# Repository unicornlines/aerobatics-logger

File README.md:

# Aerobatics Flight Logger

An onboard flight data logger and an Apple debrief app (iOS, iPadOS, macOS) for aerobatics training.

The specification lives in the project's spec document. This repository holds:

- `hardware/`: the KiCad schematic and PCB
- `firmware/`: the STM32H723 on-board firmware (planned)
- `app/`: the SwiftUI debrief app (planned)

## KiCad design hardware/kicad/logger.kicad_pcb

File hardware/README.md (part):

# Hardware

Rev A draft schematic and board for the logger, in KiCad 7 format. Both are generated from code:

- `tools/design.py`: every part and every pin's net. **Edit this, not the `.kicad_sch` files.**
- `tools/mklib.py`: builds `kicad/logger.kicad_sym` for parts KiCad doesn't ship (ICM-45686, BMP390, BMM350, NEO-M9N, ESP32-C6-MINI-1, GD5F4GM8UE), with pin tables from the datasheets.
- `tools/gen.py`: writes the sheets under `kicad/`, joining nets with global labels and flagging unused pins.
- `tools/check.py`: connectivity checks on the exported netlist (every assigned pin is on its net, power nets are driven, no output conflicts). It stands in for ERC, which the KiCad 7 command line doesn't have.

```sh
cd hardware/tools
python3 mklib.py && python3 gen.py
kicad-cli sch export netlist ../kicad/logger.kicad_sch -o /tmp/logger.net
python3 check.py /tmp/logger.net
kicad-cli sch export pdf ../kicad/logger.kicad_sch -o ../kicad/logger.pdf
```

`kicad/logger.pdf` is the latest export, for review without KiCad.

## Board

- 138 x 62 mm, 4 layers, 1.6 mm: F.Cu signals and GND pour, In1 solid GND, In2 +3V3 pour with a few signal runs, B.Cu signals and GND pour. Every part is SMD; the only parts on the back are the three key sockets. The outline is a plain rounded rectangle with no cut-outs or slots, since the board takes repeated g loads in aerobatics.
- Rules: 0.15 mm track and clearance, 0.5/0.25 mm vias, 0.4 mm for the power path.
- Front face: the Sharp 2.7-inch memory LCD at the top (7 mm right of the board's centre since the left end grew 14 mm for the GNSS patch), the three keys (UP, OK / PWR, DOWN) centred under it. Under the panel only parts up to 2.9 mm tall: the MCU with its crystals, the log flash, the 3.3 V buck and the LCD's 5 V boost and FPC socket.
- Floor plan around the panel: radio (top-left corner, antenna up), the GNSS module and its built-in patch antenna on the left, sensors below them; USB-C and microSD on the right short edge (the card goes in through the case wall), the charger, USB protection and power latch beside them; the battery socket (plug in from the right edge) and its protection in the bottom-right corner, with the logo beside the DOWN key. Passives sit in straight rows and columns next to the pins they serve.
- Top edge: radio antenna, Qwiic socket (J63), camera/marker socket (J62, JST SUR, for a lead inside the case) and the LCD's FPC fold.
- The IMU moved from the Bosch BMI563 (still not on sale) to the TDK ICM-45686 on 2026-11-25.
- The magnetometer sits at the left end, as far as possible from the buck and the battery currents; the barometer sits bottom-left beside the UP key at (22.5, 53.5), with a part-free ring round it where the case seals its hood: open to cockpit air, or with a barb for the static-port hose.
- Environmental chamber: the Sensirion SHT40 (cockpit temperature and humidity) and the top-port microphone sit together at the left edge, in one chamber the case walls off and vents through the left side wall (no openings in the face). The SHT40 sits on a copper-free island (no pour on any layer, 0.15 mm traces) instead of a milled slot, so the board's heat reaches it only through four thin traces.
- Microphone: an ST MP34DT06J top-port PDM MEMS mic (122.5 dB SPL acoustic overload) on the front, in the environmental chamber below the SHT40. Engine RPM and sound events go into the log.
- Storage: flights are logged to the soldered 512 MB GigaDevice GD5F4GM8UE flash next to the MCU (about 4.5 hours of raw logging; stocked at JLCPCB); the microSD keeps a backup copy and serves firmware updates and export.
- GNSS antennas (owner, 2026-11-26: a built-in antenna, an external one optional, no pre-fitted pigtail): a Taoglas SGGP.18.4.A.08 18 x 18 x 4 mm ceramic patch (AE1) sits right of the NEO module, with ground plane all round it and nothing on any layer within 3 x 4 mm of its feed. An edge-mount SMA (J50, Samtec SMA-J-P-H-ST-EM1) on the left edge takes an external active antenna through the case wall. An Infineon BGS12WN6 switch (U18) between them picks the patch by hardware default (pull-up on ANT_SEL, also while the MCU is in reset).
- External antenna detection: the antenna feed is switched by the MCU (Q50, AO3401A) and measured (1 ohm shunt, INA180A1, 20 mV per mA into PC2_C). Firmware turns the feed on and switches to the SMA when 3-60 mA flows; above 80 mA it treats the line as shorted, turns the feed off and retries every 5 s. The 22 ohm 2010 resistor keeps a dead short at 140 mA (0.43 W of 0.75 W) even if the firmware never reacts. The module's own VCC_RF is unused. External antennas: active, 2.7-5 V, up to 30 mA (about 3.0 V at the jack at 15 mA).
- RF lines (module to switch, switch to patch, switch to SMA): 50 ohm grounded coplanar waveguide on F.Cu over the In1 plane, 0.34 mm wide with 0.45 mm gaps (a rule in `kicad/logger.kicad_dru`; the router gets a 0.45 mm class for these nets), hand-routed and locked in `tools/pcb.py` (RF_TRACKS) with a ground via fence. The SMA branch carries a 47 pF DC block at the switch, and the bias tee (47 nH, ferrite, 100 nF) and an ESD diode at the jack.
- Radio: ESP32-C6-MINI-1 in the top-left corner, flush with the top edge. Its antenna sits over a copper keep-out on every layer (the module footprint's rule area); there is no board cut-out, which keeps the board free of stress risers. The case wall in front of it must be plastic. It may stay on in flight (fine from an avionics point of view); bulk Wi-Fi transfers happen on the ground. Planned uses: camera start/stop over Bluetooth, wireless firmware updates for both chips, compressed flight download.
- Silkscreen: references only for ICs, connectors with function labels instead (UP, OK / PWR, DOWN, CHG, BAT 1S +/−, SWD, CAM/MRK, I2C, LCD, D+/D-), IMU axes left of U6. Passive references are on F.Fab for assembly. Dwgs.User carries the LCD outline, its active area and FPC, and the 18 x 15.2 mm key caps for the case design.
- Top: the Unicornlines logo (9.5 mm, bottom-right, outside the panel) with "UNICORNLINES®" and "Never Stop Dreaming". Back: "AEROBATICS LOGGER", the revision, and *PER PERFECTIONEM AD FELICITATEM*.
- The logo is `art/unicornlines-logo.svg`, turned into the `logger:Unicornlines_Logo` silkscreen footprint by `tools/mklogo.py` (strokes thickened to the 0.16 mm silk minimum). Re-run it only when the artwork changes: `python3 mklogo.py ../art/unicornlines-logo.svg Unicornlines_Logo 9.5`.
- Four M3 holes in the corners, 4 mm in, grounded. Each has a 7 mm copper ring on every layer, so no parts, tracks or vias come closer than 3.65 mm to its centre; the case clamps the board there. (A fifth hole by the IMU was dropped on 2026-11-26: the cell lies behind the middle of the board.)

Mechanical data for the case (mm from the board's top-left corner, y down; heights above F.Cu or below B.Cu):

| Item | Position | Height | Notes |
| --- | --- | --- | --- |
| LCD module LS027B7DH01 | x 44.6-107.4, y 2.5-45.32 | glass back at 3.5, top about 4.8 | 62.8 x 42.82 x 1.3; active area 58.80 x 35.28, 2.0 mm from the FPC-far edge. Hold it on its border with a spacer frame and the bezel. FPC 9.5 mm wide, centred, leaves the top edge and folds 180° under the glass (never toward the front polariser) into J61 at (76, 6.5); the fold may stand 0-1 mm past the top board edge |
| Keys SW1-3 | (54 / 76 / 98, 53.9) | Choc V1 switch on F.Cu; socket 1.85 below B.Cu | Kailh hotswap sockets on B.Cu (the only parts on the back); the case front is the switch plate (13.8 mm square cut-outs, Choc plate thickness 1.2 mm). Caps 18 x 15.2 (case thread) |
| Tallest front part outside the panel | C34 (14, 54.5) | 5.4 | RTC/GNSS backup cap |
| USB-C J1 | right edge, centred y 14 | 3.3 | lip about 0.2 past the edge |
| microSD J60 | right edge, centred y 31.5 | 1.7 | body ends about 1 mm inside the edge; an inserted card stands about 4.5 mm out |
| Battery J2 (JST PH, side entry) | body x 118.8-129, y 39.9-51.1; pins at x 121.05 (+ y 43.5, NTC 45.5, − 47.5) | 4.85 | opening faces the right edge at x 129, plug in along −x. The front strip x 129-138, y 43-49 is free of parts for the plug and the lead, which the case turns down into a wall gully to the cell. Clear of the corner screw H4 (ring from x 130.5, y 54.5) |
| Camera/marker J62 (JST SUR) | (60.5, 2.9) | 1.75 | plug from the top edge |
| Qwiic J63 (JST SH) | (49, 3.4) | 2.9 | plug from the top edge |
| Environmental chamber | x 0.5-7.5, y 40.5-52.5; no other part within 1.2 mm | 1.0 | holds U17 SHT40 (3.0, 43.0, 0.5 high) on its copper-free island (x 1.9-6.5, y 40.8-45.2) and MK1 MP34DT06J (3.8, 49.3, 3 x 4 x 1, top port). The case baffles it off from the cavity and vents it through the left wall; free air over both parts, no foam or glue on the SHT40 |
| GNSS patch AE1 (Taoglas SGGP.18.4.A.08) | centre (32.5, 27.5); body x 23.5-41.5, y 18.5-36.5 | 4.0 | ceramic on top of the board. Only plastic above and round it: no metal inserts, screws, foil or metallic paint within about 10 mm, nothing resting on it; the display carrier's left wall stays at x 42 or more. Sky view through the face |
| GNSS SMA J50 (edge mount) | left edge, axis at y 13.0, about 0.45 above the top face | body 6.6 wide, from 3.7 above the top face to 1.2 below the bottom face | the jack (1/4"-36 thread) stands about 9.5 mm out past the left edge. The case wall passes the thread and must carry the cable's torque on the body, not on the solder joints; dust cap when unused |
| Barometer U7 (BMP390) | (22.5, 53.5) | 0.8 | the front is free of parts in x 19.45-25.55, y 50.45-56.55 (1.8 mm round the courtyard) for the hood's seal ring; only tented vias and tracks under it. Its caps C42 / C43 sit just above the ring, at (21.9, 49.4) and (23.3, 49.4) |

Rebuild (needs KiCad 7 Python and a Freerouting 2.x jar):

```sh
cd hardware/tools
python3 pcb.py && python3 seed.py old.kicad_pcb && python3 route.py /path/to/freerouting.jar
```

`pcb.py` builds the placed, unrouted board from `design.py` plus its placement table, and `route.py` routes, pours and runs DRC. Freerouting is random and this board sits near the limit of what it finishes in one go, so after a small change run `python3 seed.py <last good logger.kicad_pcb>` between the two: it copies the last clean board's copper for every net whose pads did not change and that clashes with nothing new, and leaves only the rest to the router (`git show HEAD:hardware/kicad/logger.kicad_pcb > old.kicad_pcb` gives the last committed board). The committed board is DRC-clean (0 errors, 0 unconnected). The only warnings are the "library not in this configuration" notes from a headless KiCad without the global footprint table.

Renders: `tools/render/` turns the board into a GLB (KiCad STEP export, then OCCT), plots the layers into board textures and renders the views with three.js in headless Chromium. Parts KiCad has no 3D model for here (NEO-M9N, ESP32-C6 module, TPS62130, BQ24074, BQ29700, TPS61222, Choc switches and their hotswap sockets, battery fuse, BMP390, BMM350, SHT40, MP34DT06J, flash, inductors, JST and FPC sockets, 32 kHz crystal) are drawn as plain boxes. The LCD panel is left off so the parts under it show.

| Top | Bottom |
| --- | --- |
|  |  |

## Sheets

| Sheet | Contents |
| --- | --- |
| Power | USB-C sink (CC level read by the ADC to set the input current), TVS and USB ESD, TI BQ24074 1S Li-ion linear charger with power path (charge current and input limit set by resistors: 0.25 A / 0.44 A by hardware, 1.0 A / 1.39 A switched in by the MCU; 0-50 °C window from the NTC in the battery pack; safety timer), soft power latch on the buck's EN (OK key, MCU hold line, USB power), charge LED, on-board cell protection (TI BQ29700 with two low-side AO3400A FETs) and a 3 A fuse, 3-pin JST-PH battery socket (1 cell −, 2 NTC, 3 cell +) with reverse-polarity PMOS, battery voltage to the ADC, TPS62130 buck to 3.3 V, VDDA filter, MCP65R41 power-fail comparator |
| MCU | STM32H723VGT6, decoupling, 25 MHz and 32.768 kHz crystals, RTC/GNSS backup supercap, SWD on Tag-Connect TC2030-NL pads (no part height under the panel), status LED |
| Sensors | TDK ICM-45686 IMU (SPI1, ±32 g, ±4000 °/s), BMP390 barometer (SPI2), BMM350 magnetometer (I2C1) with its 1.8 V LDO, Sensirion SHT40 temperature / humidity (I2C1, 0x44), ST MP34DT06J PDM microphone (DFSDM1 channel 1) |
| GNSS | NEO-M9N (25 Hz, JLCPCB stock); built-in Taoglas 18 mm patch and an edge SMA for an external active antenna, chosen by a BGS12WN6 RF switch; switched, current-measured antenna feed (detects an external antenna and shorts). VDD_USB grounded (USB unused). A NEO-F9P drops in with the same wiring (L1 on the patch, L5 needs an external antenna) |
| IO | GD5F4GM8UEYIG 4 Gbit (512 MB) log flash on OCTOSPI1 (quad): the main flight log. microSD (SDMMC1) as backup copy, firmware update and export path. Sharp LS027B7DH01 2.7-inch 400 x 240 memory LCD on SPI4 (Panasonic AYF531035 FPC socket, TPS61222 5 V boost, VCOM toggled by TIM15_CH1), three Kailh Choc keys in hotswap sockets (UP, OK / PWR, DOWN; OK is also the power key on the power sheet), camera-sync and marker socket (J62, JST SUR: sync out, GND, marker in), Qwiic I2C expansion socket (J63, I2C4, PTC-fused 3V3) for an optional airspeed sensor |
| Radio | ESP32-C6-MINI-1 (Wi-Fi 6, BLE 5) as an SPI4 slave sharing SCK/MOSI with the LCD, IRQ line, EN and boot straps driven by the MCU, UART0 to the MCU for flashing, USB D-/D+ test pads |

## Open items

- [x] ICM-45686: pin table checked against DS-000577 section 4.1 (via a page-referenced extraction of the datasheet): RESV pins 2, 3, 7, 10, 11 may be NC, VDDIO or GND, so they stay open with their internal pull-ups on; 0.1 uF X7R on VDD and on VDDIO as specified; VDD 1.71 to 3.6 V and VDDIO 1.08 to 3.6 V cover 3.3 V. Axis arrows (pin 1 top-left, +X right, +Y up, +Z out of the top) match TDK's convention and CogniPilot's footprint silk for this part. Firmware: turn off the internal pull-ups on the four active SPI pins.
- [x] BMP390 pin table (DS002 table 52) and BMM350 ball table (DS001 section 6, top view) match the symbols. BMM350: BYPASS to GND, CRST 2.2 uF to GND, ADSEL low = 0x14, VDD 1.72 to 1.98 V (AP2112K-1.8 gives 1.77 to 1.83 V). Ball map matches four independent footprints.
- [x] Memory LCD (2026-11-26): Sharp LS027B7DH01 pin table and timing from Sharp's LD-28305A spec (SPI write-only, LSB first, SCS active high, up to 1-2 MHz; EXTMODE high, EXTCOMIN 1-20 Hz from TIM15_CH1 on PE5, DISP on PD10, pulled low so the panel stays blank until firmware runs). FPC pin order checked against the Adafruit 2.7-inch breakout and two other open designs. 5 V from a TPS61222 (4.82-5.13 V) per its datasheet; the panel draws 50-350 µW.
- [x] LCD socket Panasonic AYF531035 (Y5B, 10 pins, 0.5 mm, 1.0 mm high, Sharp's recommended part): signal lands 0.3 x 0.8 mm, 3.30 mm pattern depth, FPC enters on the signal-land side. The holding lands (1.0 x 0.8 mm, centres 6.36 mm apart) are read from Panasonic's dimension table, whose drawing could not be fetched as an image; they cover the community variants. Worth a look at the drawing before ordering.
- [x] GNSS: NEO-M9N pin table from data sheet UBX-19014285 section 3 (same as SparkFun's symbol). Antenna bias tee after u-blox's active-antenna circuit (NEO-F9P integration manual 4.4.4.3): BLM15HB121SH1 ferrite, 100 nF, 47 nH LQG15HS47NJ02 (keeps >500 ohm down to L5 for the F9P); the feed now comes from +3V3 through a switch and a 1 + 22 ohm sense and limit instead of VCC_RF (u-blox: keep a short below 150 mA, 19 ohm or more at 3.3 V).
- [x] Antenna switch BGS12WN6 (Infineon data sheet rev 2.9): pins 1 RF2, 2 GND, 3 RF1, 4 VDD, 5 RFIN, 6 CTRL as KiCad's symbol and PG-TSNP-6-10 footprint; CTRL high selects RF2 (patch), VIH 1.0 V, VDD 1.65-3.6 V; no DC on RF ports, hence the 47 pF block on the SMA branch. INA180A1 (SOT-23-5: 1 OUT, 2 GND, 3 IN+, 4 IN-, 5 V+) and AO3401A (1 G, 2 S, 3 D) as the KiCad symbols. Patch land pattern: eight 5 x 5 mm ground pads on a 6 mm grid and a 2.0 x 2.5 mm feed 7.6 mm from the centre, cross-checked with two open SGGP.18.4 footprints.
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
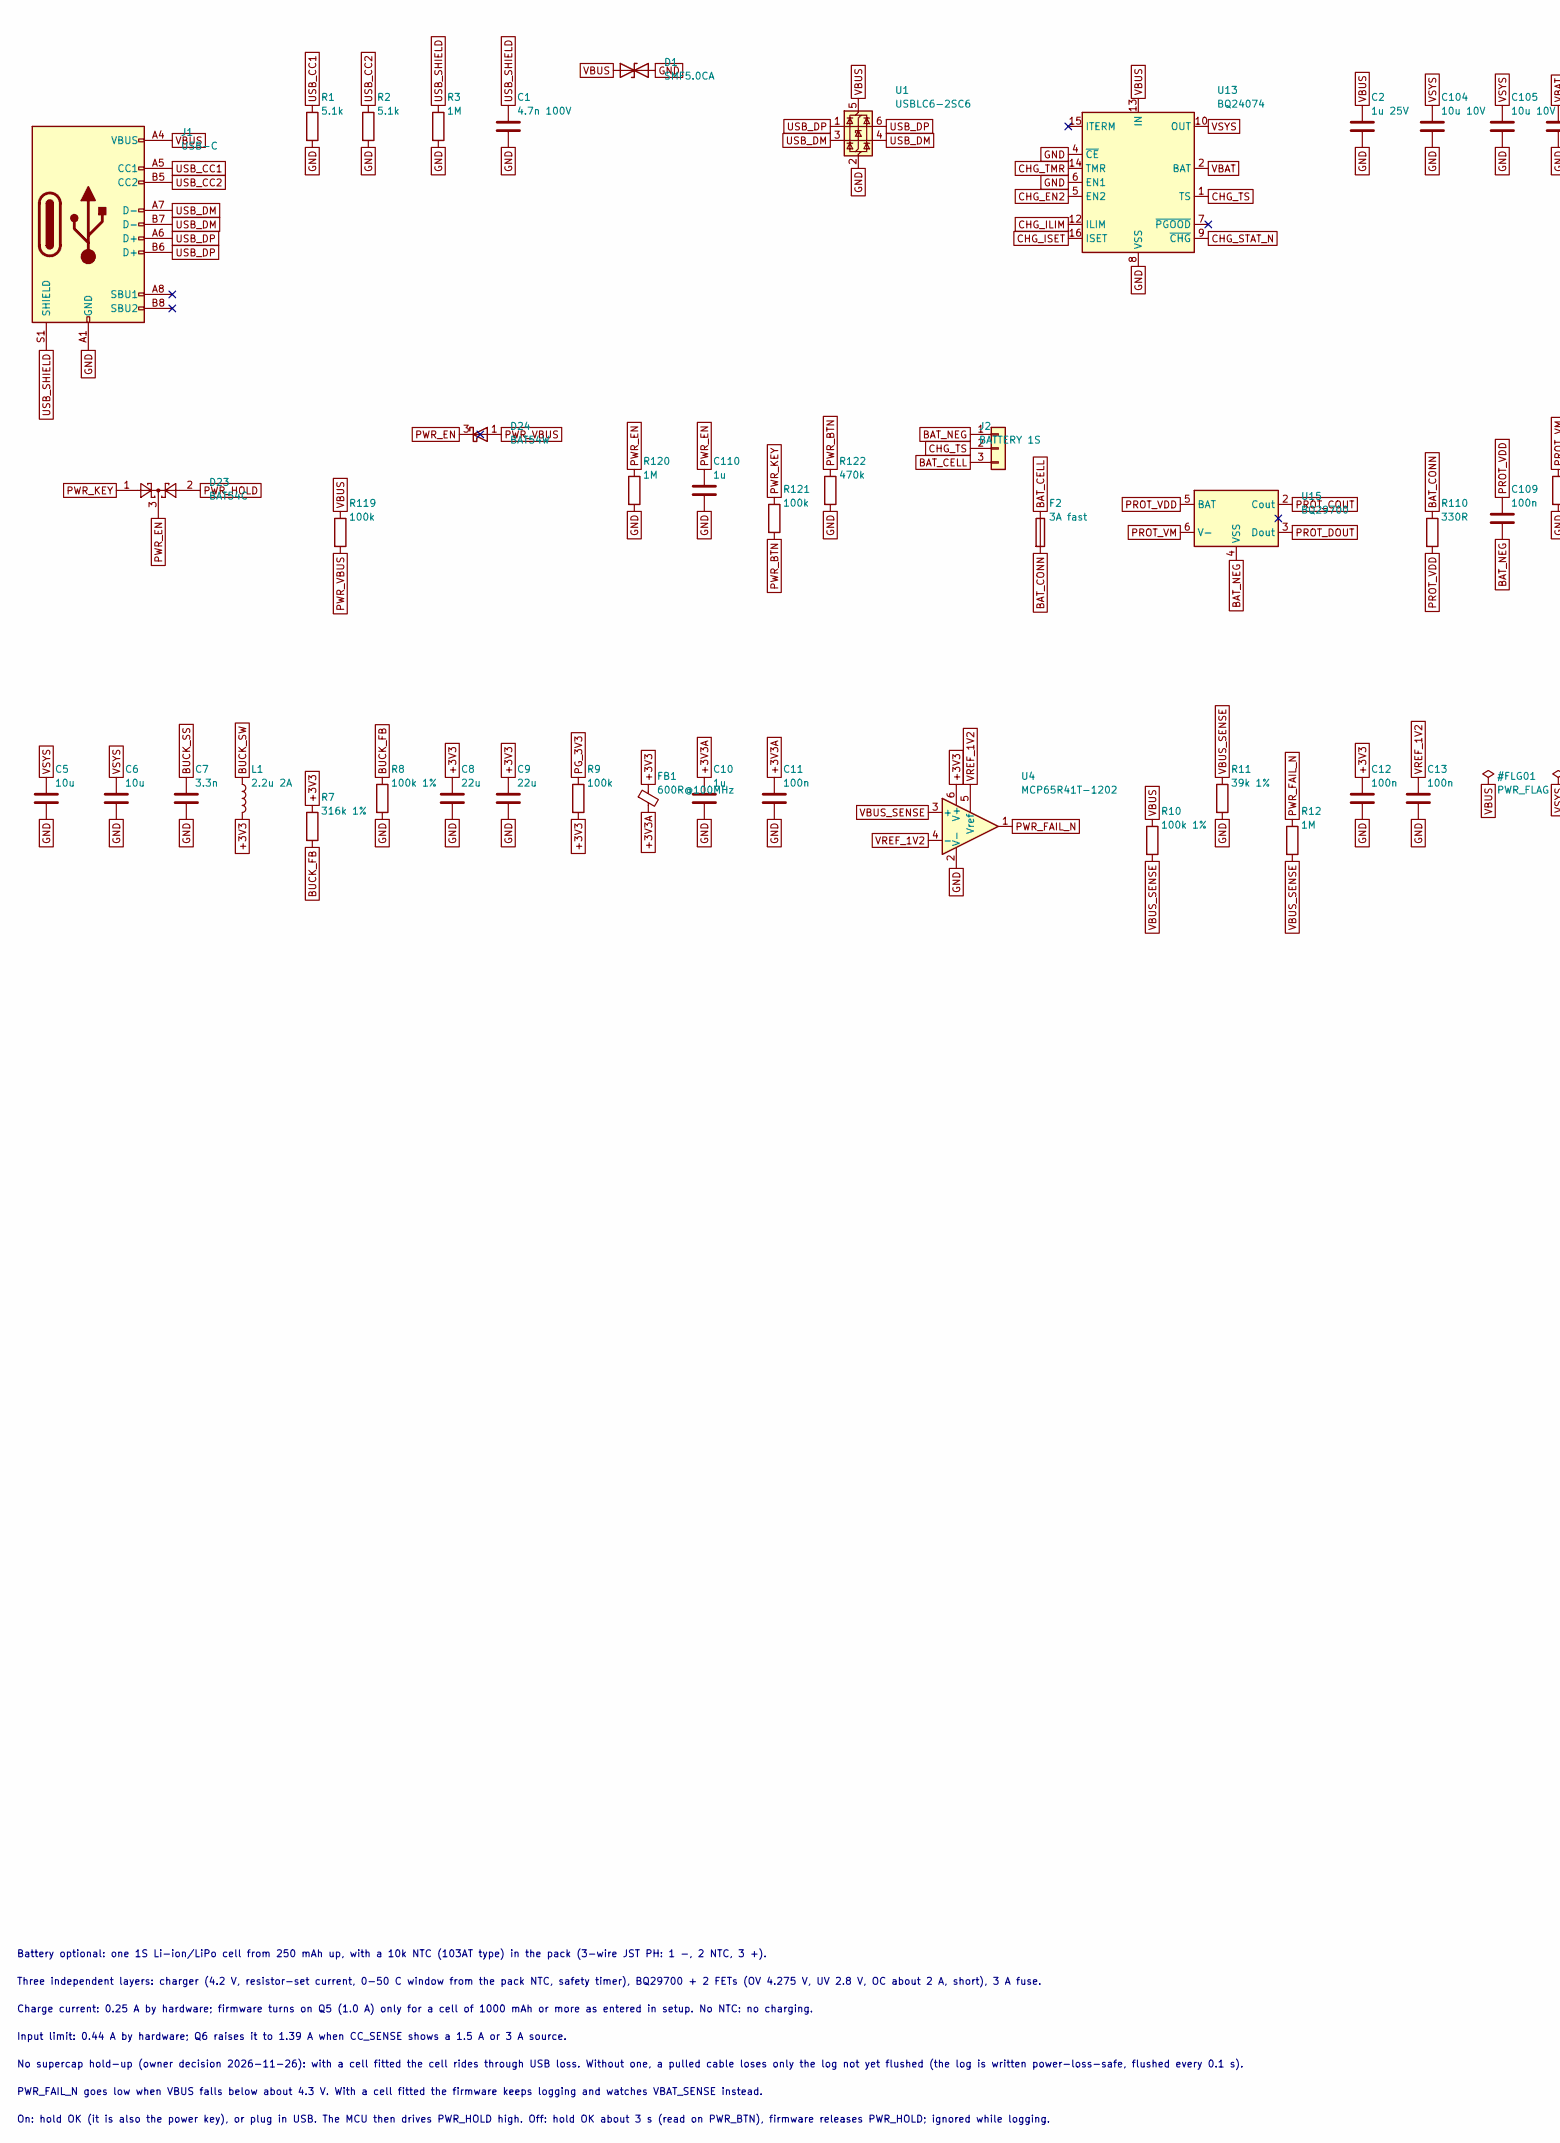
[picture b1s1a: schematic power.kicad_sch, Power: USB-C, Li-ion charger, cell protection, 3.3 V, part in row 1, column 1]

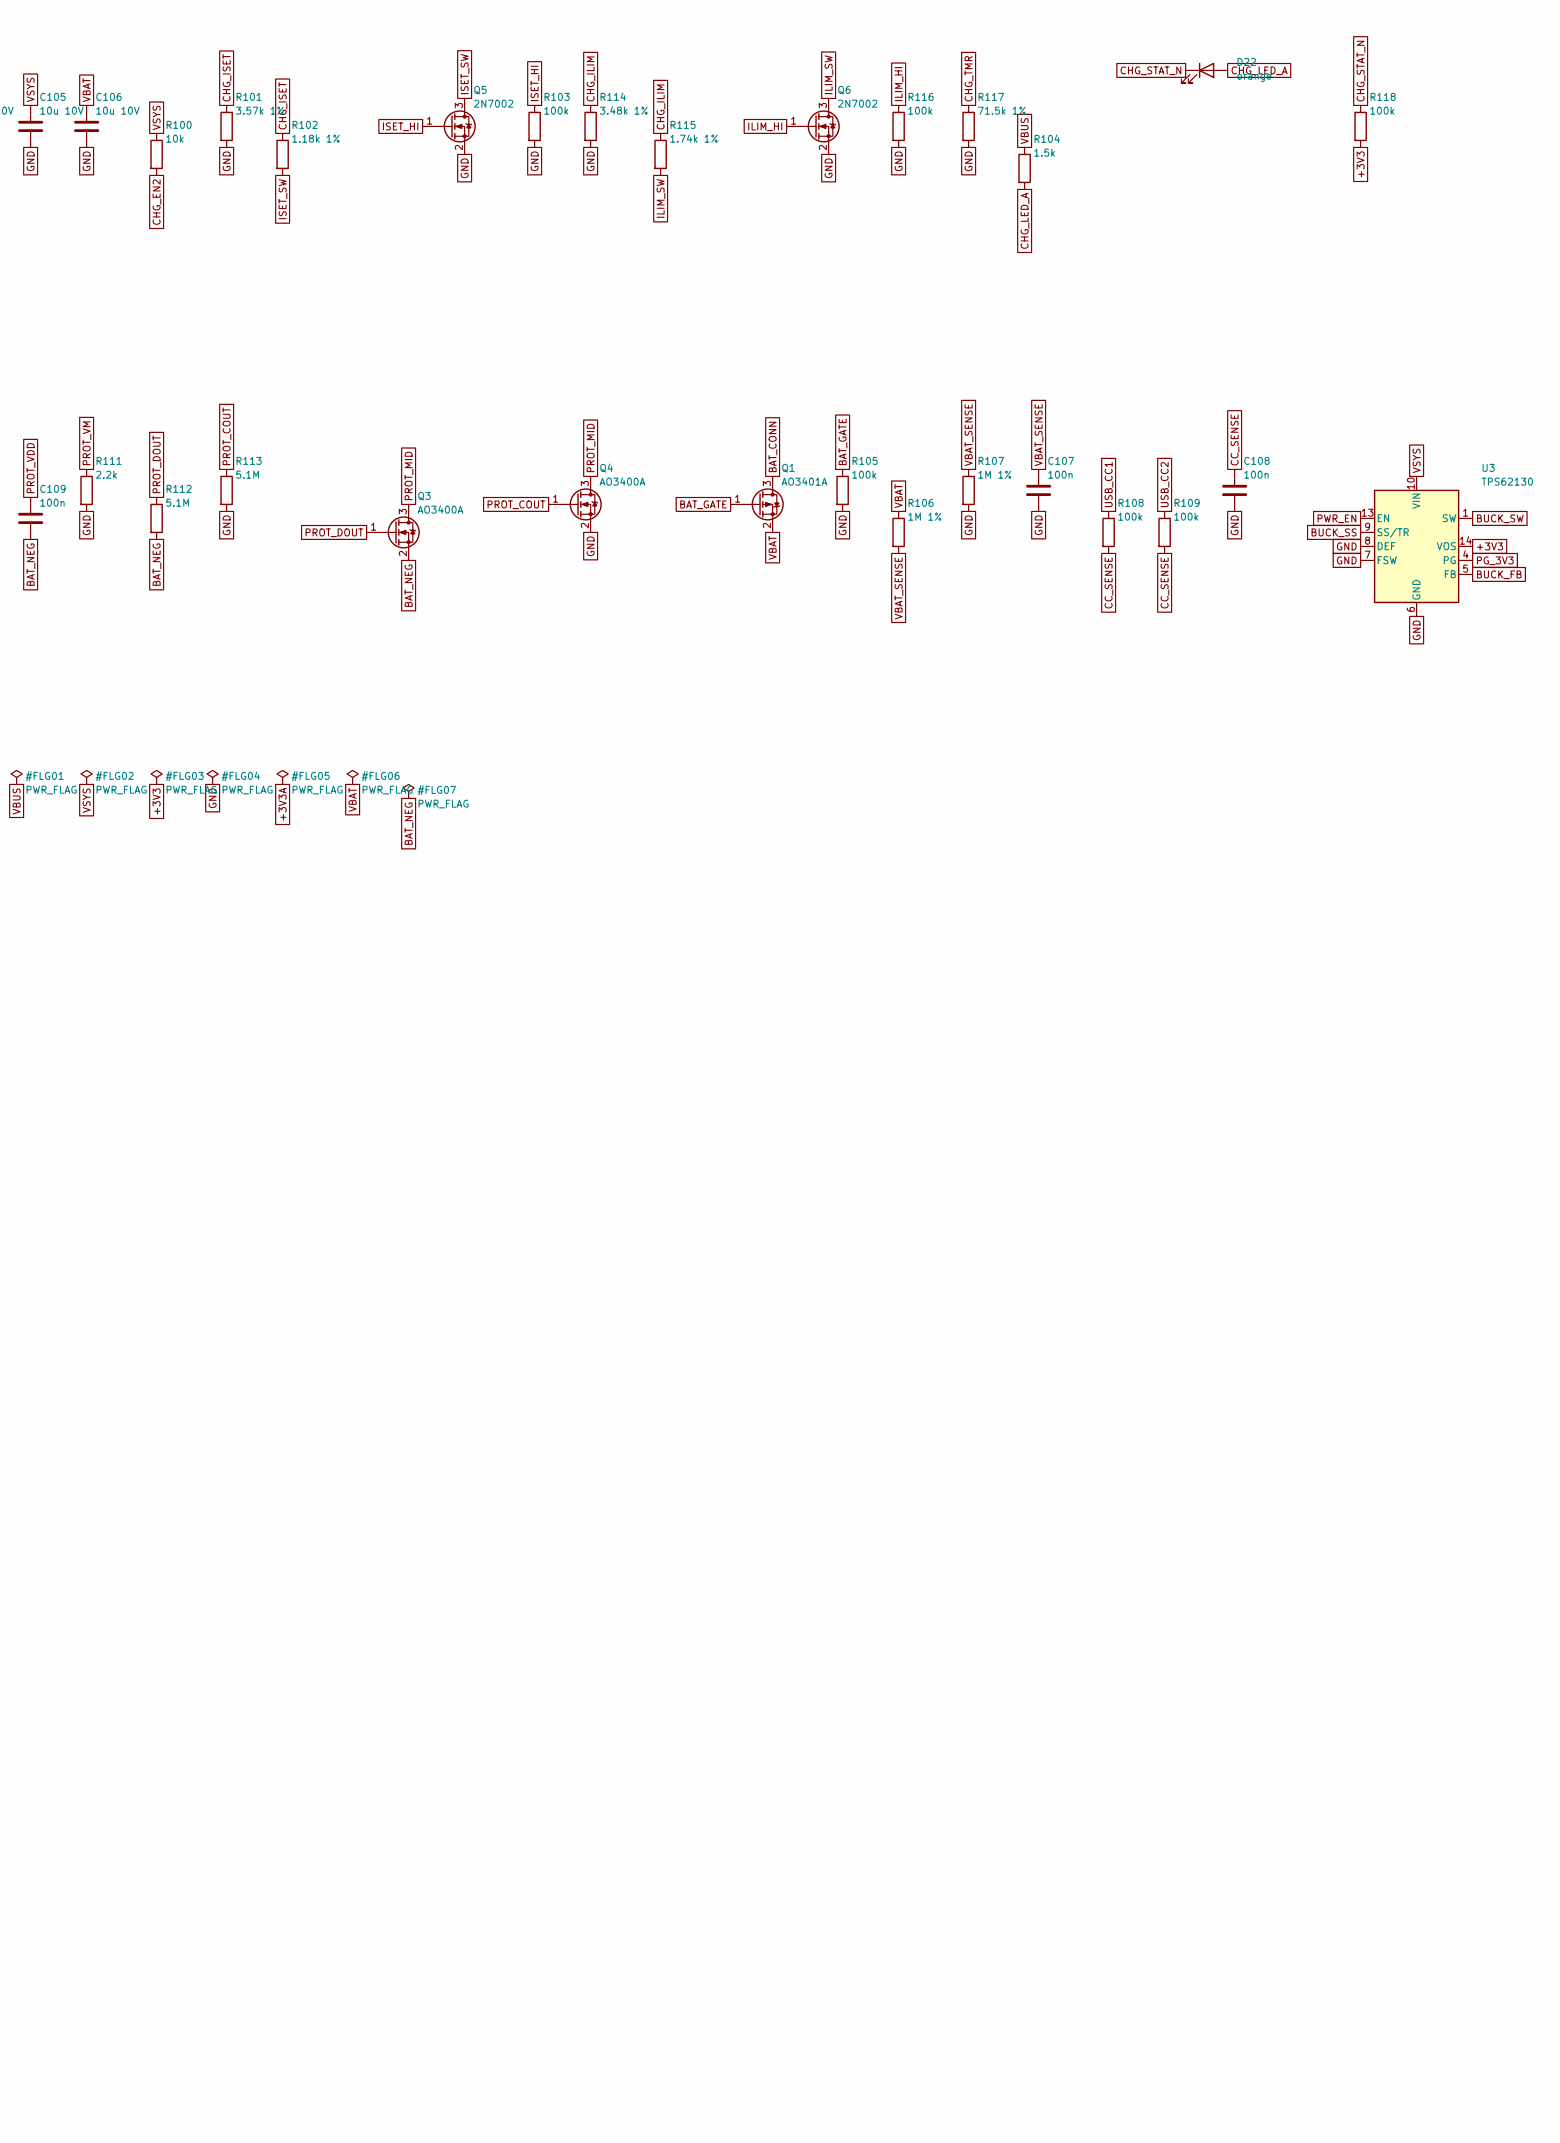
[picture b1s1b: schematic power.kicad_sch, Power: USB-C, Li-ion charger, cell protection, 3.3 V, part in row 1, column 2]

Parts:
C1: 4.7n 100V; C_0603_1608Metric
C2: 1u 25V; C_0603_1608Metric
C5, C6: 10u; C_0805_2012Metric
C7: 3.3n; C_0402_1005Metric
C8, C9: 22u; C_0805_2012Metric
C10, C110: 1u; C_0402_1005Metric
C11, C12, C13, C107, C108, C109: 100n; C_0402_1005Metric
C104, C105, C106: 10u 10V; C_0805_2012Metric
D1: SMF5.0CA; D_SOD-123F
D22: orange; LED_0603_1608Metric
D23: BAT54C; SOT-23; MPN BAT54C
D24: BAT54W; SOT-323_SC-70; MPN BAT54W
F2: 3A fast; Fuse_1206_3216Metric; MPN 0466003.NR
FB1: 600R@100MHz; L_0603_1608Metric
J1: USB-C; USB_C_Receptacle_GCT_USB4105-xx-A_16P_TopMnt_Horizontal
J2: BATTERY 1S; JST_PH_S3B-PH-SM4-TB_1x03-1MP_P2.00mm_Horizontal; MPN S3B-PH-SM4-TB(LF)(SN)
L1: 2.2u 2A; L_1210_3225Metric
Q1: AO3401A; SOT-23; MPN AO3401A
Q3, Q4: AO3400A; SOT-23; MPN AO3400A
Q5, Q6: 2N7002; SOT-23; MPN 2N7002
R1, R2: 5.1k; R_0402_1005Metric
R3, R12, R120: 1M; R_0402_1005Metric
R7: 316k 1%; R_0402_1005Metric
R8, R10: 100k 1%; R_0402_1005Metric
R9, R103, R105, R108, R109, R116, R118, R119, R121: 100k; R_0402_1005Metric
R11: 39k 1%; R_0402_1005Metric
R100: 10k; R_0402_1005Metric
R101: 3.57k 1%; R_0402_1005Metric
R102: 1.18k 1%; R_0402_1005Metric
R104: 1.5k; R_0402_1005Metric
R106, R107: 1M 1%; R_0402_1005Metric
R110: 330R; R_0402_1005Metric
R111: 2.2k; R_0402_1005Metric
R112, R113: 5.1M; R_0402_1005Metric
R114: 3.48k 1%; R_0402_1005Metric
R115: 1.74k 1%; R_0402_1005Metric
R117: 71.5k 1%; R_0402_1005Metric
R122: 470k; R_0402_1005Metric
U1: USBLC6-2SC6; SOT-23-6
U3: TPS62130; VQFN-16-1EP_3x3mm_P0.5mm_EP1.68x1.68mm
U4: MCP65R41T-1202; SOT-23-6
U13: BQ24074; VQFN-16-1EP_3x3mm_P0.5mm_EP1.68x1.68mm; MPN BQ24074RGTR
U15: BQ29700; WSON-6_1.5x1.5mm_P0.5mm; MPN BQ29700DSER

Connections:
+3V3: C8.1, C9.1, C12.1, FB1.1, L1.2, R7.1, R9.2, R118.2, U3.14 (VOS), U4.6 (V+); also elsewhere on the board
+3V3A: C10.1, C11.1, FB1.2; also elsewhere on the board
BAT_CELL: F2.1, J2.3
BAT_CONN: F2.2, Q1.3 (D), R110.1
BAT_GATE: Q1.1 (G), R105.1
BAT_NEG: C109.2, J2.1, Q3.2 (S), R112.2, U15.4 (VSS)
BUCK_FB: R7.2, R8.1, U3.5 (FB)
BUCK_SS: C7.1, U3.9 (SS/TR)
BUCK_SW: L1.1, U3.1 (SW), U3.2 (SW), U3.3 (SW)
CC_SENSE: C108.1, R108.2, R109.2; also elsewhere on the board
CHG_EN2: R100.2, U13.5 (EN2)
CHG_ILIM: R114.1, R115.1, U13.12 (ILIM)
CHG_ISET: R101.1, R102.1, U13.16 (ISET)
CHG_LED_A: D22.2 (A), R104.2
CHG_STAT_N: D22.1 (K), R118.1, U13.9 (~CHG); also elsewhere on the board
CHG_TMR: R117.1, U13.14 (TMR)
CHG_TS: J2.2, U13.1 (TS)
GND: C1.2, C2.2, C5.2, C6.2, C7.2, C8.2, C9.2, C10.2, C11.2, C12.2, C13.2, C104.2, C105.2, C106.2, C107.2, C108.2, C110.2, D1.2 (A2), J1.A1 (GND), J1.A12 (GND), J1.B1 (GND), J1.B12 (GND), J2.MP, Q4.2 (S), Q5.2 (S), Q6.2 (S), R1.2, R2.2, R3.2, R8.2, R11.2, R101.2, R103.2, R105.2, R107.2, R111.2, R113.2, R114.2, R116.2, R117.2, R120.2, R122.2, U1.2 (GND), U3.6 (GND), U3.7 (FSW), U3.8 (DEF), U3.15 (GND), U3.16 (GND), U3.17 (GND), U4.2 (V-), U13.4 (~CE), U13.6 (EN1), U13.8 (VSS), U13.17 (VSS); also elsewhere on the board
ILIM_HI: Q6.1 (G), R116.1; also elsewhere on the board
ILIM_SW: Q6.3 (D), R115.2
ISET_HI: Q5.1 (G), R103.1; also elsewhere on the board
ISET_SW: Q5.3 (D), R102.2
PG_3V3: R9.1, U3.4 (PG)
PROT_COUT: Q4.1 (G), R113.1, U15.2 (Cout)
PROT_DOUT: Q3.1 (G), R112.1, U15.3 (Dout)
PROT_MID: Q3.3 (D), Q4.3 (D)
PROT_VDD: C109.1, R110.2, U15.5 (BAT)
PROT_VM: R111.1, U15.6 (V-)
PWR_BTN: R121.2, R122.1; also elsewhere on the board
PWR_EN: C110.1, D23.3, D24.3 (K), R120.1, U3.13 (EN)
PWR_FAIL_N: R12.1, U4.1; also elsewhere on the board
PWR_HOLD: D23.2; also elsewhere on the board
PWR_KEY: D23.1, R121.1; also elsewhere on the board
PWR_VBUS: D24.1 (A), R119.2
USB_CC1: J1.A5 (CC1), R1.1, R108.1
USB_CC2: J1.B5 (CC2), R2.1, R109.1
USB_DM: J1.A7 (D-), J1.B7 (D-), U1.3 (I/O2), U1.4 (I/O2); also elsewhere on the board
USB_DP: J1.A6 (D+), J1.B6 (D+), U1.1 (I/O1), U1.6 (I/O1); also elsewhere on the board
USB_SHIELD: C1.1, J1.S1 (SHIELD), R3.1
VBAT: C106.1, Q1.2 (S), R106.1, U13.2 (BAT), U13.3 (BAT)
VBAT_SENSE: C107.1, R106.2, R107.1; also elsewhere on the board
VBUS: C2.1, D1.1 (A1), J1.A4 (VBUS), J1.A9 (VBUS), J1.B4 (VBUS), J1.B9 (VBUS), R10.1, R104.1, R119.1, U1.5 (VBUS), U13.13 (IN)
VBUS_SENSE: R10.2, R11.1, R12.2, U4.3 (+)
VREF_1V2: C13.1, U4.4 (-), U4.5 (Vref)
VSYS: C5.1, C6.1, C104.1, C105.1, R100.1, U3.10 (VIN), U3.11 (VIN), U3.12 (VIN), U13.10 (OUT), U13.11 (OUT); also elsewhere on the board

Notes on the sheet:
Battery optional: one 1S Li-ion/LiPo cell from 250 mAh up, with a 10k NTC (103AT type) in the pack (3-wire JST PH: 1 -, 2 NTC, 3 +).
Three independent layers: charger (4.2 V, resistor-set current, 0-50 C window from the pack NTC, safety timer), BQ29700 + 2 FETs (OV 4.275 V, UV 2.8 V, OC about 2 A, short), 3 A fuse.
Charge current: 0.25 A by hardware; firmware turns on Q5 (1.0 A) only for a cell of 1000 mAh or more as entered in setup. No NTC: no charging.
Input limit: 0.44 A by hardware; Q6 raises it to 1.39 A when CC_SENSE shows a 1.5 A or 3 A source.
No supercap hold-up (owner decision 2026-11-26): with a cell fitted the cell rides through USB loss. Without one, a pulled cable loses only the log not yet flushed (the log is written power-loss-safe, flushed every 0.1 s).
PWR_FAIL_N goes low when VBUS falls below about 4.3 V. With a cell fitted the firmware keeps logging and watches VBAT_SENSE instead.
On: hold OK (it is also the power key), or plug in USB. The MCU then drives PWR_HOLD high. Off: hold OK about 3 s (read on PWR_BTN), firmware releases PWR_HOLD; ignored while logging.

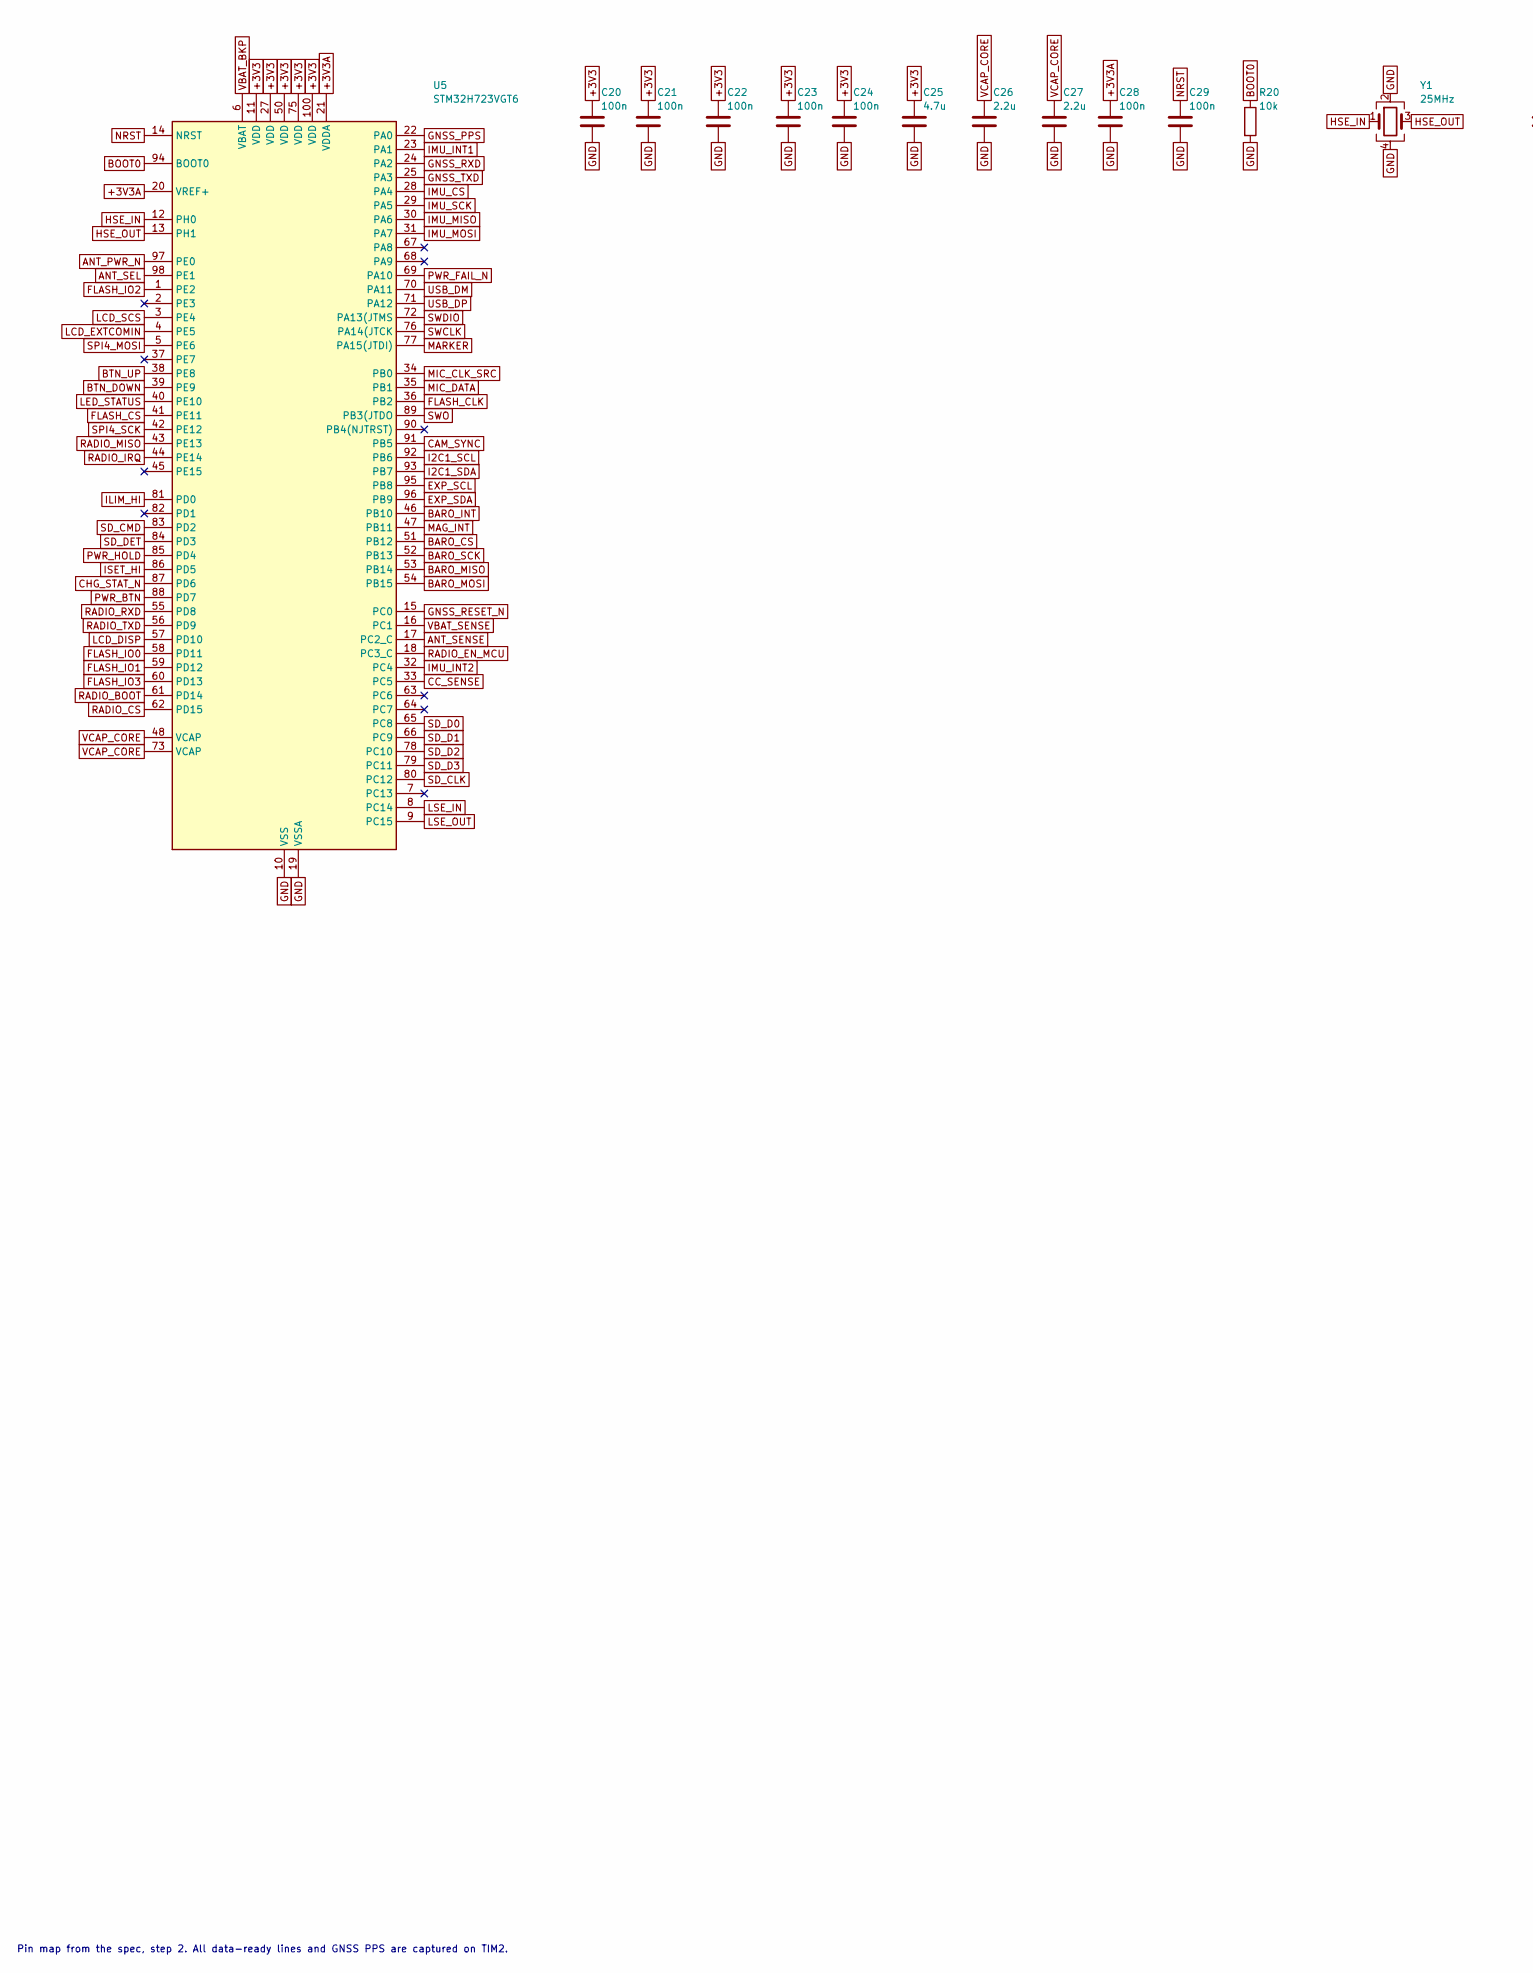
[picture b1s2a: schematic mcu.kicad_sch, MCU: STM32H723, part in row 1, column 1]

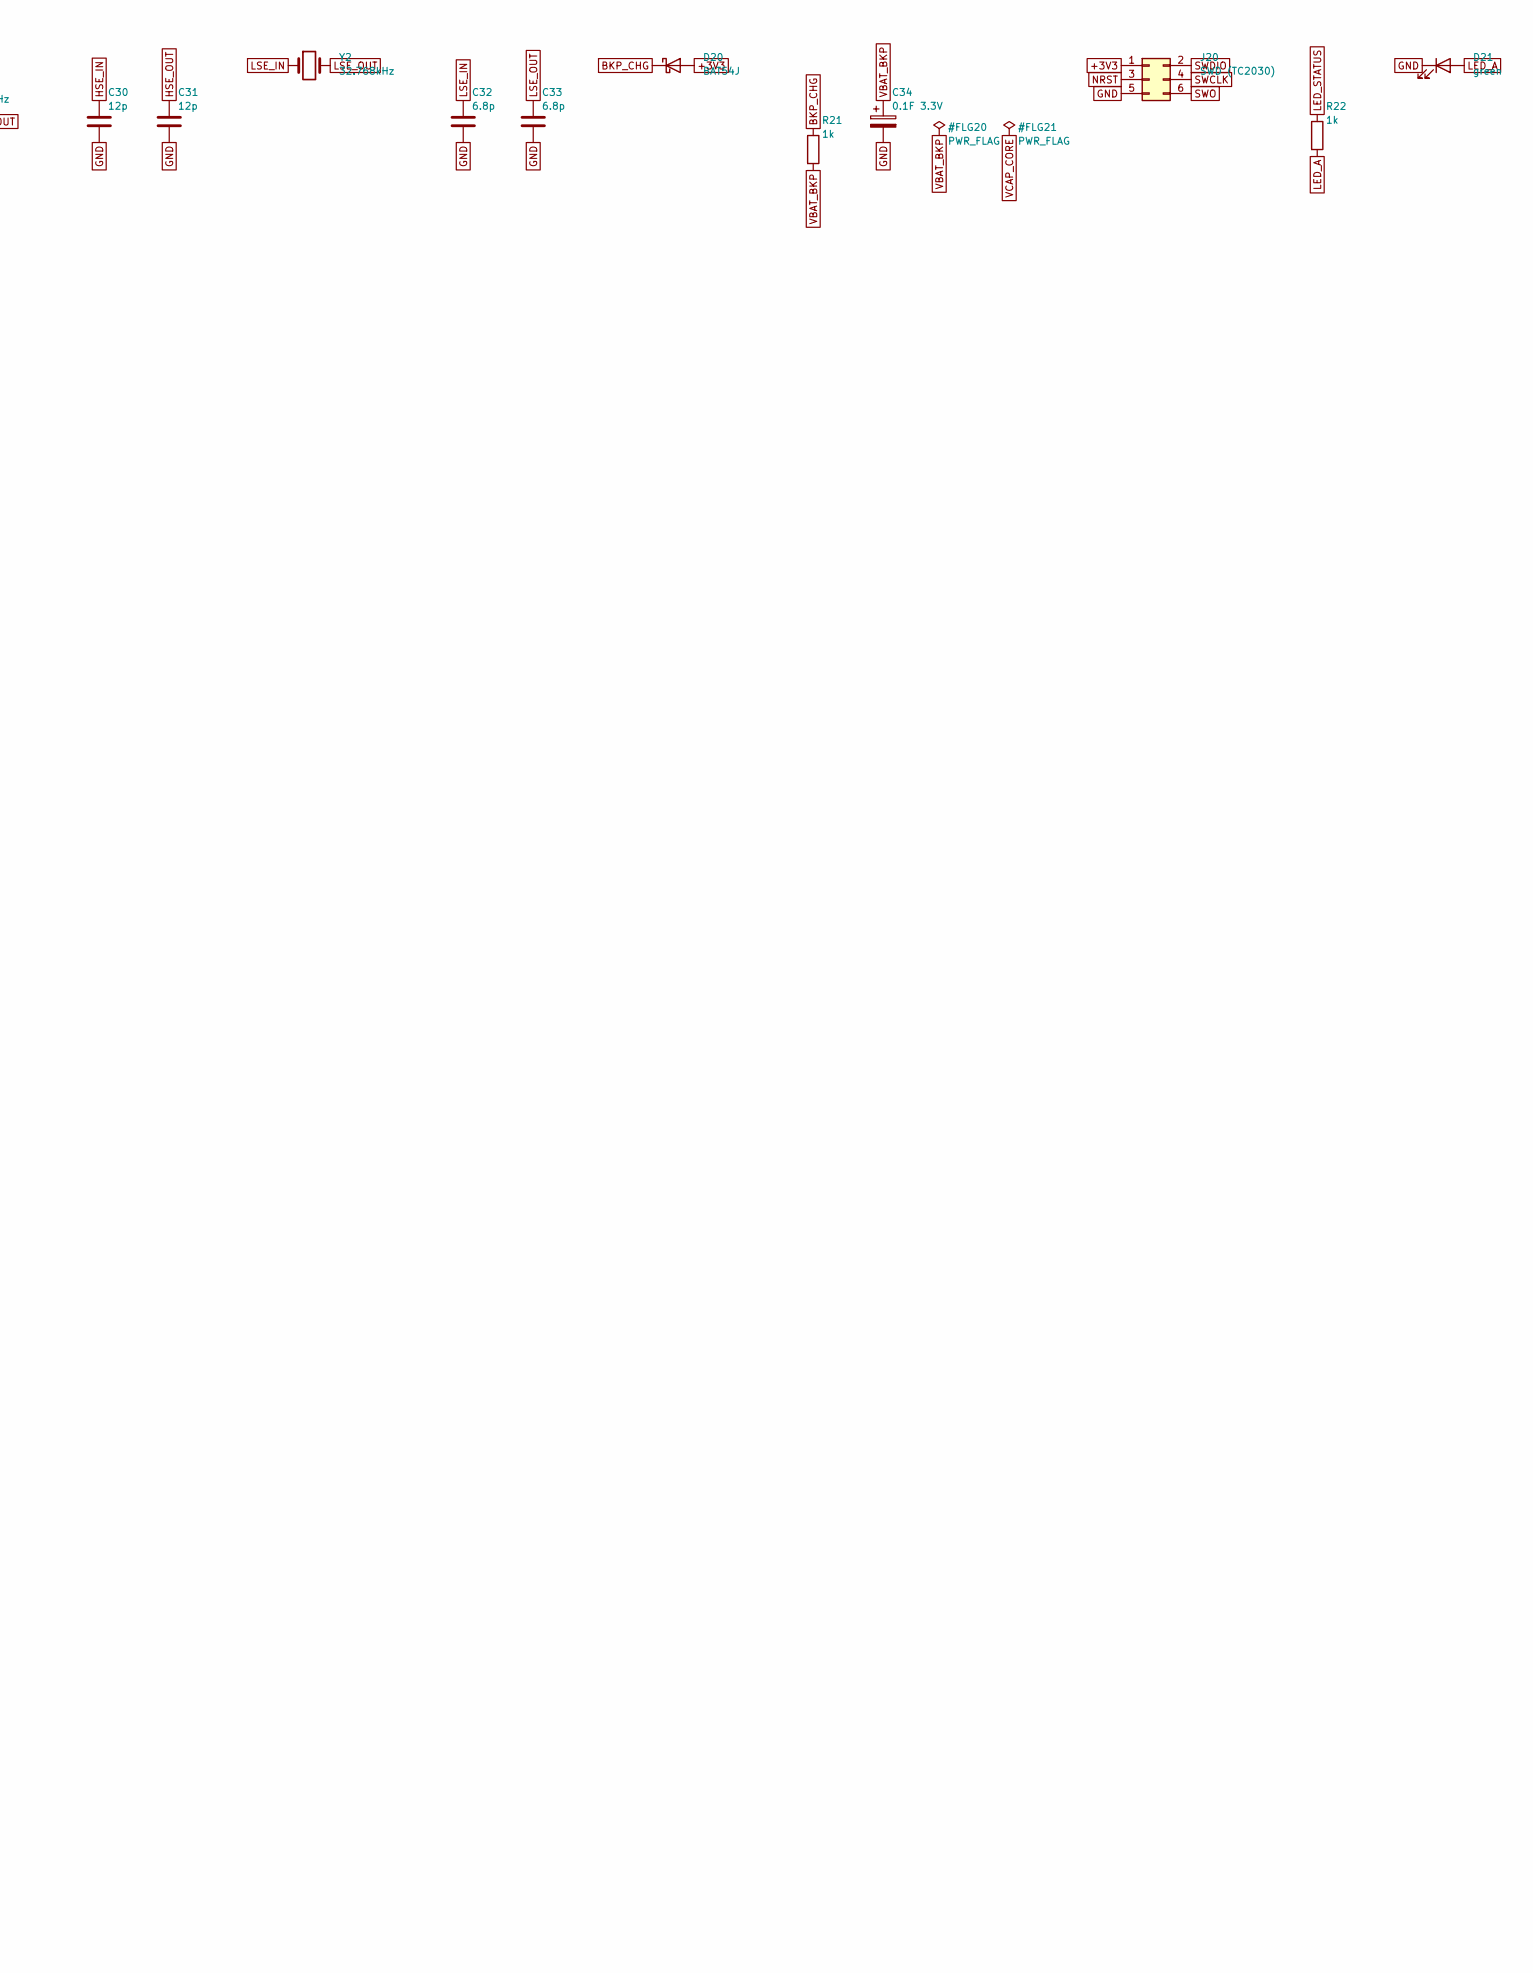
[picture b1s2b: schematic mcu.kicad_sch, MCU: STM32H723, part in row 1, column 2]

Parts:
C20, C21, C22, C23, C24, C28, C29: 100n; C_0402_1005Metric
C25: 4.7u; C_0603_1608Metric
C26, C27: 2.2u; C_0603_1608Metric
C30, C31: 12p; C_0402_1005Metric
C32, C33: 6.8p; C_0402_1005Metric
C34: 0.1F 3.3V; CP_Elec_5x5.4
D20: BAT54J; D_SOD-323F
D21: green; LED_0603_1608Metric
J20: SWD (TC2030); Tag-Connect_TC2030-IDC-NL_2x03_P1.27mm_Vertical
R20: 10k; R_0402_1005Metric
R21, R22: 1k; R_0402_1005Metric
U5: STM32H723VGT6; LQFP-100_14x14mm_P0.5mm
Y1: 25MHz; Crystal_SMD_3225-4Pin_3.2x2.5mm
Y2: 32.768kHz; Crystal_SMD_2012-2Pin_2.0x1.2mm

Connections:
+3V3: C20.1, C21.1, C22.1, C23.1, C24.1, C25.1, D20.2 (A), J20.1, U5.11 (VDD), U5.27 (VDD), U5.50 (VDD), U5.75 (VDD), U5.100 (VDD); also elsewhere on the board
+3V3A: C28.1, U5.20 (VREF+), U5.21 (VDDA); also elsewhere on the board
ANT_PWR_N: U5.97 (PE0); also elsewhere on the board
ANT_SEL: U5.98 (PE1); also elsewhere on the board
ANT_SENSE: U5.17 (PC2_C); also elsewhere on the board
BARO_CS: U5.51 (PB12); also elsewhere on the board
BARO_INT: U5.46 (PB10); also elsewhere on the board
BARO_MISO: U5.53 (PB14); also elsewhere on the board
BARO_MOSI: U5.54 (PB15); also elsewhere on the board
BARO_SCK: U5.52 (PB13); also elsewhere on the board
BKP_CHG: D20.1 (K), R21.1
BOOT0: R20.1, U5.94 (BOOT0)
BTN_DOWN: U5.39 (PE9); also elsewhere on the board
BTN_UP: U5.38 (PE8); also elsewhere on the board
CAM_SYNC: U5.91 (PB5); also elsewhere on the board
CC_SENSE: U5.33 (PC5); also elsewhere on the board
CHG_STAT_N: U5.87 (PD6); also elsewhere on the board
EXP_SCL: U5.95 (PB8); also elsewhere on the board
EXP_SDA: U5.96 (PB9); also elsewhere on the board
FLASH_CLK: U5.36 (PB2); also elsewhere on the board
FLASH_CS: U5.41 (PE11); also elsewhere on the board
FLASH_IO0: U5.58 (PD11); also elsewhere on the board
FLASH_IO1: U5.59 (PD12); also elsewhere on the board
FLASH_IO2: U5.1 (PE2); also elsewhere on the board
FLASH_IO3: U5.60 (PD13); also elsewhere on the board
GND: C20.2, C21.2, C22.2, C23.2, C24.2, C25.2, C26.2, C27.2, C28.2, C29.2, C30.2, C31.2, C32.2, C33.2, C34.2, D21.1 (K), J20.5, R20.2, U5.10 (VSS), U5.19 (VSSA), U5.26 (VSS), U5.49 (VSS), U5.74 (VSS), U5.99 (VSS), Y1.2, Y1.4; also elsewhere on the board
GNSS_PPS: U5.22 (PA0); also elsewhere on the board
GNSS_RESET_N: U5.15 (PC0); also elsewhere on the board
GNSS_RXD: U5.24 (PA2); also elsewhere on the board
GNSS_TXD: U5.25 (PA3); also elsewhere on the board
HSE_IN: C30.1, U5.12 (PH0), Y1.1
HSE_OUT: C31.1, U5.13 (PH1), Y1.3
I2C1_SCL: U5.92 (PB6); also elsewhere on the board
I2C1_SDA: U5.93 (PB7); also elsewhere on the board
ILIM_HI: U5.81 (PD0); also elsewhere on the board
IMU_CS: U5.28 (PA4); also elsewhere on the board
IMU_INT1: U5.23 (PA1); also elsewhere on the board
IMU_INT2: U5.32 (PC4); also elsewhere on the board
IMU_MISO: U5.30 (PA6); also elsewhere on the board
IMU_MOSI: U5.31 (PA7); also elsewhere on the board
IMU_SCK: U5.29 (PA5); also elsewhere on the board
ISET_HI: U5.86 (PD5); also elsewhere on the board
LCD_DISP: U5.57 (PD10); also elsewhere on the board
LCD_EXTCOMIN: U5.4 (PE5); also elsewhere on the board
LCD_SCS: U5.3 (PE4); also elsewhere on the board
LED_A: D21.2 (A), R22.2
LED_STATUS: R22.1, U5.40 (PE10)
LSE_IN: C32.1, U5.8 (PC14), Y2.1
LSE_OUT: C33.1, U5.9 (PC15), Y2.2
MAG_INT: U5.47 (PB11); also elsewhere on the board
MARKER: U5.77 (PA15(JTDI)); also elsewhere on the board
MIC_CLK_SRC: U5.34 (PB0); also elsewhere on the board
MIC_DATA: U5.35 (PB1); also elsewhere on the board
NRST: C29.1, J20.3, U5.14 (NRST)
PWR_BTN: U5.88 (PD7); also elsewhere on the board
PWR_FAIL_N: U5.69 (PA10); also elsewhere on the board
PWR_HOLD: U5.85 (PD4); also elsewhere on the board
RADIO_BOOT: U5.61 (PD14); also elsewhere on the board
RADIO_CS: U5.62 (PD15); also elsewhere on the board
RADIO_EN_MCU: U5.18 (PC3_C); also elsewhere on the board
RADIO_IRQ: U5.44 (PE14); also elsewhere on the board
RADIO_MISO: U5.43 (PE13); also elsewhere on the board
RADIO_RXD: U5.55 (PD8); also elsewhere on the board
RADIO_TXD: U5.56 (PD9); also elsewhere on the board
SD_CLK: U5.80 (PC12); also elsewhere on the board
SD_CMD: U5.83 (PD2); also elsewhere on the board
SD_D0: U5.65 (PC8); also elsewhere on the board
SD_D1: U5.66 (PC9); also elsewhere on the board
SD_D2: U5.78 (PC10); also elsewhere on the board
SD_D3: U5.79 (PC11); also elsewhere on the board
SD_DET: U5.84 (PD3); also elsewhere on the board
SPI4_MOSI: U5.5 (PE6); also elsewhere on the board
SPI4_SCK: U5.42 (PE12); also elsewhere on the board
SWCLK: J20.4, U5.76 (PA14(JTCK)
SWDIO: J20.2, U5.72 (PA13(JTMS)
SWO: J20.6, U5.89 (PB3(JTDO)
USB_DM: U5.70 (PA11); also elsewhere on the board
USB_DP: U5.71 (PA12); also elsewhere on the board
VBAT_BKP: C34.1, R21.2, U5.6 (VBAT); also elsewhere on the board
VBAT_SENSE: U5.16 (PC1); also elsewhere on the board
VCAP_CORE: C26.1, C27.1, U5.48 (VCAP), U5.73 (VCAP)

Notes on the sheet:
Pin map from the spec, step 2. All data-ready lines and GNSS PPS are captured on TIM2.
